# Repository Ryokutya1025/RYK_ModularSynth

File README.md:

# RYK ModularSynth Projects

## 概要
個人制作モジュラーシンセサイザーの電子工作・回路設計プロジェクト集です。

## プロジェクト一覧
| Project Name | Status | Model Number | Description | Link |
|----------|----------|----------|----------|----------|
| EuroRack | ✅Designed | RYK-EUR_A1 | ウォルナット×レザーデザインのユーロラック | 🚧WIP |
| PSU | ✅Designed | RYK-PSU-A1 | 多段π型フィルタ搭載PSU<br>C0.1μF, C1μF, C1000μF, L22μH, C1000μF, C1μF, C0.1μF | [✅PSU](https://github.com/Ryokutya1025/RYK_ModularSynth/tree/main/PSU) |
| BusBoard | ✅Designed | RYK-BSB-A1 | ノイズフィルタ搭載バスボード<br>C0.1μF, C1μF, C47μFデカップリング | [✅Busboard](https://github.com/Ryokutya1025/RYK_ModularSynth/tree/main/BusBoard) |
| SSI2130-VCO | 🚧WIP | RYK-VCO2130-A1 | SSI2130を使用したアナログVCO | 🚧WIP |

## 使用ソフト・機器
 <br>
 <br>
<br>
 <br>

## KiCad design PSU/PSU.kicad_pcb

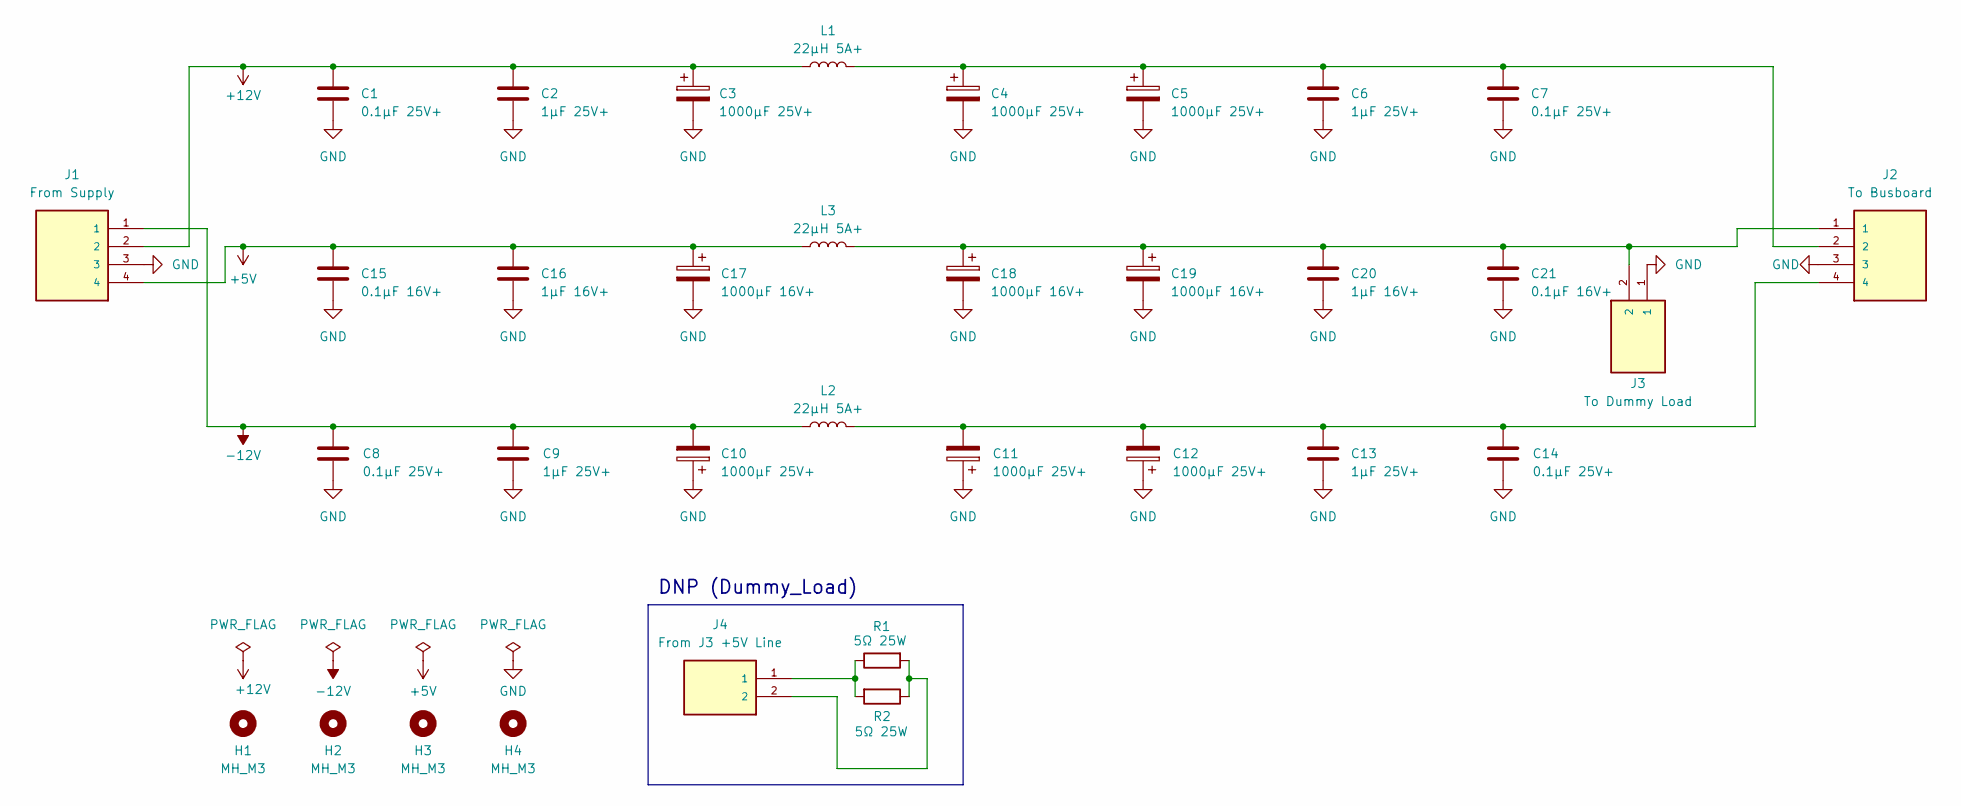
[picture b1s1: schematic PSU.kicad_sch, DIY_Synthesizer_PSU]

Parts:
C1, C7, C8, C14: 0.1µF 25V+; C_Disc_D5.0mm_W2.5mm_P5.00mm
C2, C6, C9, C13: 1µF 25V+; C_Disc_D5.1mm_W3.2mm_P5.00mm
C3, C4, C5, C10, C11, C12: 1000µF 25V+; CP_Radial_D13.0mm_P5.00mm
C15, C21: 0.1µF 16V+; C_Disc_D5.0mm_W2.5mm_P5.00mm
C16, C20: 1µF 16V+; C_Disc_D5.1mm_W3.2mm_P5.00mm
C17, C18, C19: 1000µF 16V+; CP_Radial_D13.0mm_P5.00mm
H1, H2, H3, H4: MH_M3; MountingHole_3.2mm_M3
J1: From Supply; CUI_TB002-500-04BE
J2: To Busboard; CUI_TB002-500-04BE
J3: To Dummy Load; CUI_TB002-500-02BE
J4: From J3 +5V Line; CUI_TB002-500-02BE
L1, L2, L3: 22µH 5A+; L_Radial_D12.0mm_P10.00mm_Neosid_SD12_style1
R1, R2: 5Ω 25W

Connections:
+5V: C15.1, C16.1, C17.1, J1.4, L3.1
+12V: C1.1, C2.1, C3.1, J1.2, L1.1
-12V: C8.2, C9.2, C10.2, J1.1, L2.2
GND: C1.2, C2.2, C3.2, C4.2, C5.2, C6.2, C7.2, C8.1, C9.1, C10.1, C11.1, C12.1, C13.1, C14.1, C15.2, C16.2, C17.2, C18.2, C19.2, C20.2, C21.2, J1.3, J2.3, J3.1
unnamed: C4.1, C5.1, C6.1, C7.1, J2.2, L1.2
unnamed: C11.2, C12.2, C13.2, C14.2, J2.4, L2.1
unnamed: C18.1, C19.1, C20.1, C21.1, J2.1, J3.2, L3.2
unnamed: J4.1, R1.1, R2.2
unnamed: J4.2, R1.2, R2.1

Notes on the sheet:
DNP (Dummy_Load)

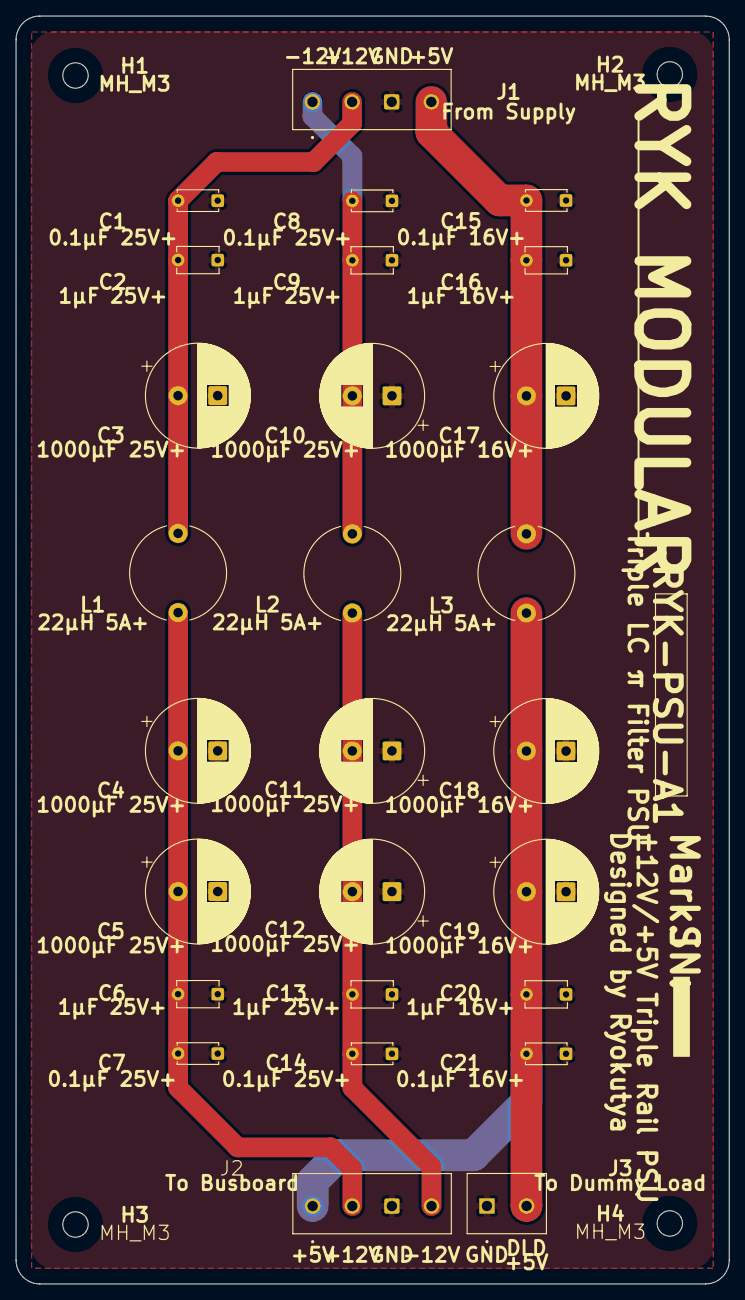
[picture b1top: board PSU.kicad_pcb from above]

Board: 2 copper layers, 90.0 x 160.0 mm, 31 parts (0 on the bottom side), 7 nets.

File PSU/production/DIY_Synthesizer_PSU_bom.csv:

Designator,Footprint,Quantity,Value,LCSC Part #
"C1, C14, C7, C8",C_Disc_D5.0mm_W2.5mm_P5.00mm,4,0.1µF 25V+,
"C10, C11, C12, C3, C4, C5",CP_Radial_D13.0mm_P5.00mm,6,1000µF 25V+,
"C13, C2, C6, C9",C_Disc_D5.1mm_W3.2mm_P5.00mm,4,1µF 25V+,
"C15, C21",C_Disc_D5.0mm_W2.5mm_P5.00mm,2,0.1µF 16V+,
"C16, C20",C_Disc_D5.1mm_W3.2mm_P5.00mm,2,1µF 16V+,
"C17, C18, C19",CP_Radial_D13.0mm_P5.00mm,3,1000µF 16V+,
J1,CUI_TB002-500-04BE,1,From Supply,
J2,CUI_TB002-500-04BE,1,To BusBoard,
J3,CUI_TB002-500-02BE,1,To Dummy_Load,
"L1, L2, L3",L_Radial_D12.0mm_P10.00mm_Neosid_SD12_style1,3,22µH 5A+,

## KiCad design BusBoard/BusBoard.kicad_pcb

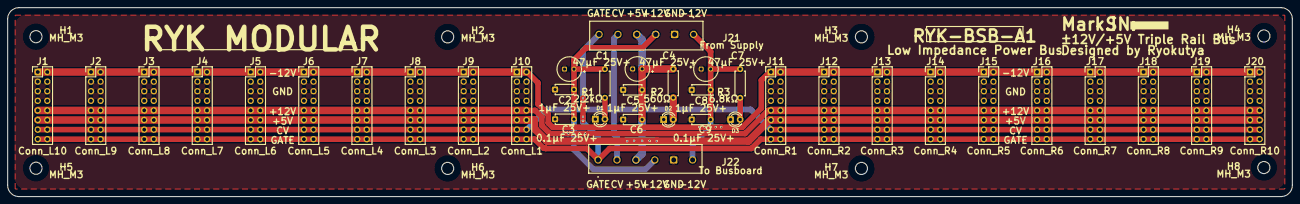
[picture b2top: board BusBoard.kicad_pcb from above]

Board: 2 copper layers, 340.0 x 50.0 mm, 45 parts (0 on the bottom side), 9 nets.

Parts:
C1, C4, C7: 47µF 25V+; WCAP-AT1H_6.3X11_DXL_
C2, C5, C8: 1µF 25V+; C_Disc_D4.7mm_W2.5mm_P5.00mm
C3, C6, C9: 0.1µF 25V+; C_Disc_D4.7mm_W2.5mm_P5.00mm
D1: LED_Red; LED_D3.0mm
D2: LED_Grean; LED_D3.0mm
D3: LED_Blue; LED_D3.0mm
H1, H2, H3, H4, H5, H6, H7, H8: MH_M3; MountingHole_3.2mm_M3
J1: Conn_L10; PinHeader_2x08_P2.54mm_Vertical
J2: Conn_L9; PinHeader_2x08_P2.54mm_Vertical
J3: Conn_L8; PinHeader_2x08_P2.54mm_Vertical
J4: Conn_L7; PinHeader_2x08_P2.54mm_Vertical
J5: Conn_L6; PinHeader_2x08_P2.54mm_Vertical
J6: Conn_L5; PinHeader_2x08_P2.54mm_Vertical
J7: Conn_L4; PinHeader_2x08_P2.54mm_Vertical
J8: Conn_L3; PinHeader_2x08_P2.54mm_Vertical
J9: Conn_L2; PinHeader_2x08_P2.54mm_Vertical
J10: Conn_L1; PinHeader_2x08_P2.54mm_Vertical
J11: Conn_R1; PinHeader_2x08_P2.54mm_Vertical
J12: Conn_R2; PinHeader_2x08_P2.54mm_Vertical
J13: Conn_R3; PinHeader_2x08_P2.54mm_Vertical
J14: Conn_R4; PinHeader_2x08_P2.54mm_Vertical
J15: Conn_R5; PinHeader_2x08_P2.54mm_Vertical
J16: Conn_R6; PinHeader_2x08_P2.54mm_Vertical
J17: Conn_R7; PinHeader_2x08_P2.54mm_Vertical
J18: Conn_R8; PinHeader_2x08_P2.54mm_Vertical
J19: Conn_R9; PinHeader_2x08_P2.54mm_Vertical
J20: Conn_R10; PinHeader_2x08_P2.54mm_Vertical
J21: From Supply; CUI_TB002-500-06BE
J22: To Busboard; CUI_TB002-500-06BE
R1: 2.2kΩ; R_Axial_DIN0207_L6.3mm_D2.5mm_P7.62mm_Horizontal
R2: 560Ω; R_Axial_DIN0207_L6.3mm_D2.5mm_P7.62mm_Horizontal
R3: 6.8kΩ; R_Axial_DIN0207_L6.3mm_D2.5mm_P7.62mm_Horizontal

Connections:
+5V: C4.1, C5.1, C6.1, J1.11, J1.12, J2.11, J2.12, J3.11, J3.12, J4.11, J4.12, J5.11, J5.12, J6.11, J6.12, J7.11, J7.12, J8.11, J8.12, J9.11, J9.12, J10.11, J10.12, J11.11, J11.12, J12.11, J12.12, J13.11, J13.12, J14.11, J14.12, J15.11, J15.12, J16.11, J16.12, J17.11, J17.12, J18.11, J18.12, J19.11, J19.12, J20.11, J20.12, J21.4, J22.3, R2.1
+12V: C1.1, C2.1, C3.1, J1.9, J1.10, J2.9, J2.10, J3.9, J3.10, J4.9, J4.10, J5.9, J5.10, J6.9, J6.10, J7.9, J7.10, J8.9, J8.10, J9.9, J9.10, J10.9, J10.10, J11.9, J11.10, J12.9, J12.10, J13.9, J13.10, J14.9, J14.10, J15.9, J15.10, J16.9, J16.10, J17.9, J17.10, J18.9, J18.10, J19.9, J19.10, J20.9, J20.10, J21.3, J22.4, R1.1
-12V: C7.2, C8.1, C9.1, J1.1, J1.2, J2.1, J2.2, J3.1, J3.2, J4.1, J4.2, J5.1, J5.2, J6.1, J6.2, J7.1, J7.2, J8.1, J8.2, J9.1, J9.2, J10.1, J10.2, J11.1, J11.2, J12.1, J12.2, J13.1, J13.2, J14.1, J14.2, J15.1, J15.2, J16.1, J16.2, J17.1, J17.2, J18.1, J18.2, J19.1, J19.2, J20.1, J20.2, J21.1, J22.6, R3.1
CV: J1.13, J1.14, J2.13, J2.14, J3.13, J3.14, J4.13, J4.14, J5.13, J5.14, J6.13, J6.14, J7.13, J7.14, J8.13, J8.14, J9.13, J9.14, J10.13, J10.14, J11.13, J11.14, J12.13, J12.14, J13.13, J13.14, J14.13, J14.14, J15.13, J15.14, J16.13, J16.14, J17.13, J17.14, J18.13, J18.14, J19.13, J19.14, J20.13, J20.14, J21.5, J22.2
GATE: J1.15, J1.16, J2.15, J2.16, J3.15, J3.16, J4.15, J4.16, J5.15, J5.16, J6.15, J6.16, J7.15, J7.16, J8.15, J8.16, J9.15, J9.16, J10.15, J10.16, J11.15, J11.16, J12.15, J12.16, J13.15, J13.16, J14.15, J14.16, J15.15, J15.16, J16.15, J16.16, J17.15, J17.16, J18.15, J18.16, J19.15, J19.16, J20.15, J20.16, J21.6, J22.1
GND: C1.2, C2.2, C3.2, C4.2, C5.2, C6.2, C7.1, C8.2, C9.2, D1.1 (K), D2.1 (K), D3.2 (A), J1.3, J1.4, J1.5, J1.6, J1.7, J1.8, J2.3, J2.4, J2.5, J2.6, J2.7, J2.8, J3.3, J3.4, J3.5, J3.6, J3.7, J3.8, J4.3, J4.4, J4.5, J4.6, J4.7, J4.8, J5.3, J5.4, J5.5, J5.6, J5.7, J5.8, J6.3, J6.4, J6.5, J6.6, J6.7, J6.8, J7.3, J7.4, J7.5, J7.6, J7.7, J7.8, J8.3, J8.4, J8.5, J8.6, J8.7, J8.8, J9.3, J9.4, J9.5, J9.6, J9.7, J9.8, J10.3, J10.4, J10.5, J10.6, J10.7, J10.8, J11.3, J11.4, J11.5, J11.6, J11.7, J11.8, J12.3, J12.4, J12.5, J12.6, J12.7, J12.8, J13.3, J13.4, J13.5, J13.6, J13.7, J13.8, J14.3, J14.4, J14.5, J14.6, J14.7, J14.8, J15.3, J15.4, J15.5, J15.6, J15.7, J15.8, J16.3, J16.4, J16.5, J16.6, J16.7, J16.8, J17.3, J17.4, J17.5, J17.6, J17.7, J17.8, J18.3, J18.4, J18.5, J18.6, J18.7, J18.8, J19.3, J19.4, J19.5, J19.6, J19.7, J19.8, J20.3, J20.4, J20.5, J20.6, J20.7, J20.8, J21.2, J22.5
unnamed: D1.2 (A), R1.2
unnamed: D2.2 (A), R2.2
unnamed: D3.1 (K), R3.2

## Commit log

2026-06-02 Update README
    Added project overview and software/tools used.
2026-06-02 Update VS Code badge in README
2026-06-02 Update VS Code badge in README
    Updated VS Code badge to the latest version.
2026-06-04 Update project table and software badges in README
2026-06-04 fix 16pin layout
2026-06-04 modified .gitignore
2026-06-04 Ignore KiCad Cache Files
2026-06-04 Remove generated KiCad files
2026-06-05 modified SymbolFootPrintData
2026-06-08 add SSI2130_VCO VREF circuit
2026-06-08 add SymbolData
2026-06-09 add SYNC_IN Circuit
2026-06-12 fix sync circuit
2026-06-13 add TZ circuit
